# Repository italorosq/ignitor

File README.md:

# Serra Rocketry Ignitor

Sistema de ignição remota para foguetes experimentais. Duas estações
independentes conversam por LoRa 433 MHz.

A mesma PCB é usada nas duas estações para baratear a fabricação. O que muda é
a população e o firmware:

| Estação | Firmware | Módulos ligados |
| --- | --- | --- |
| Comando | `estacao_comando_esp.py` | botão, OLED, LEDs, buzzer, LoRa |
| Ignição | `estacao_ignicao_esp.py` | relé, Q1/Q2, LEDs, buzzer, LoRa |

Na estação de comando não são montados Q1, Q2, J7/J8/J12 nem o módulo relé. Na
ignição, o OLED (J11) não é montado. O resto da placa é comum.

## Como funciona

1. O operador segura o botão até o OLED mostrar **CONFIRMADO** (cerca de 13 s).
2. O comando transmite `ARM_CONFIRMED` a cada 200 ms.
3. A ignição responde `ACK` e começa a contagem de **10 s**.
4. Se o comando sumir por mais de **500 ms**, a ignição aborta.
5. No fim da contagem, o relé e o Q1 fecham por **2 s**.
6. A ignição envia `IGNITION_COMPLETE`. O comando mostra o resultado no OLED e
   toca o tema do Mario no buzzer.
7. Soltar o botão a qualquer momento, inclusive durante a queima, envia `ABORT`.
8. Depois da queima ou de um abort, o comando espera o botão ser solto e
   pressionado de novo antes de iniciar outro ciclo.

Ao energizar, o comando toca o tema do **Zelda**. Enquanto o botão está
pressionado, dá um bip curto por segundo. No fim da queima, toca o tema do
**Mario**. O laço de disparo usa duas chaves em série: o contato do relé e o Q1. O Q1 fica
no lado de baixo:

```text
BAT+ ── relé COM/NO ── ignitor ── J12.2 (dreno Q1)
Q1 source (J12.1) ──────────────── BAT−
```

Não ligue o ignitor entre J12.1 e J12.2: isso coloca a carga em paralelo com o
Q1. Também não inverta dreno e source; o diodo de corpo do MOSFET conduz e a
carga dispara mesmo com `GATE_2` em zero.

## Firmware

- Comando: `firmware/micropython/estacao_comando_esp.py` (ESP32 + OLED).
- Ignição: `firmware/micropython/estacao_ignicao_esp.py` (ESP32, sem OLED).
- Pico: `firmware/micropython/legacy/` (não é usado nas placas atuais).

Os dois firmwares são independentes. O comando não carrega código de relé ou
ADC; a ignição não carrega código de OLED, botão ou EXP.

## Placas

| Placa | Dimensão | Estado |
| --- | --- | --- |
| Ignição SMD | 78,8 × 57,3 mm | candidata; conferir DRC antes de fabricar |
| Ignição PTH | 75 × 80 mm | funcional; limpeza de serigrafia pendente |
| Ignição CNC | 50 × 90 mm | em projeto |

## Segurança

- Use carga dummy antes de qualquer ignitor real.
- Conecte a antena LoRa antes de energizar.
- Feche o J8 (ARM/RBF) só no momento do teste.
- Mantenha o operador a pelo menos 10 m do foguete.
- O botão de comando é momentâneo: soltar a qualquer momento aborta na hora.
  Só solte depois de o OLED mostrar `CONFIRMADO`.
- Depois de um abort ou de uma queima, solte o botão antes de tentar de novo.
- A ignição não tem botão local; o abort vem por LoRa ou pela perda de sinal.
- O link do comando é supervisão: quem corta o disparo é a ignição, em 500 ms.
- O protocolo usa ID de sistema e sequência, mas não tem criptografia. O J8
  continua sendo a barreira física.

## Documentação

- [Arquitetura](docs/ARQUITETURA.md)
- [Instalação](docs/INSTALL.md)
- [Protocolo](docs/README_API.md)
- [Estado do projeto](docs/ESTADO_DO_PROJETO.md)
- [Testes](test/README.md)

Projeto da [Serra Rocketry](https://github.com/Serra-Rocketry).

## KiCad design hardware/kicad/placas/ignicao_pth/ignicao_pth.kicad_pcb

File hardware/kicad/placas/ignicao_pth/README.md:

# Ignição PTH

Placa de 75 × 80 mm, duas camadas, quatro furos M3. Mesma topologia da SMD;
mudam os encapsulamentos (D1 1N5818, C3 de 10 µF e Q3 BC337).

## Estado

- DRC: 0 erros, 100 avisos (serigrafia e biblioteca), 0 desconexões.
- Paridade: 4 itens, todos os furos `H1`–`H4`.
- `Q1.3`/`J9.1` no GND; `Q1.2`/`J9.2` no dreno. O `J9.1` é o retorno
  BAT−/GND; o `J9.2` é o NO do relé/dreno.
- Pacote JLCPCB antigo; regenerar antes de fabricar.

## Conectores

| Ref | Uso |
| --- | --- |
| J1 | entrada 5 V |
| J2/J3 | botão (comando) |
| J4/J5 | LED do botão (comando) |
| J7 | módulo relé (ignição) |
| J8 | ARM/RBF (ignição) |
| J9 | dreno/source do Q1 (ignição) |
| J10 | buzzer |
| J11 | OLED (comando) |

## Validação

```powershell
$cli = "C:\Program Files\KiCad\10.0\bin\kicad-cli.exe"
& $cli sch erc --severity-all ignicao_pth.kicad_sch
& $cli pcb drc --severity-all --schematic-parity ignicao_pth.kicad_pcb
```

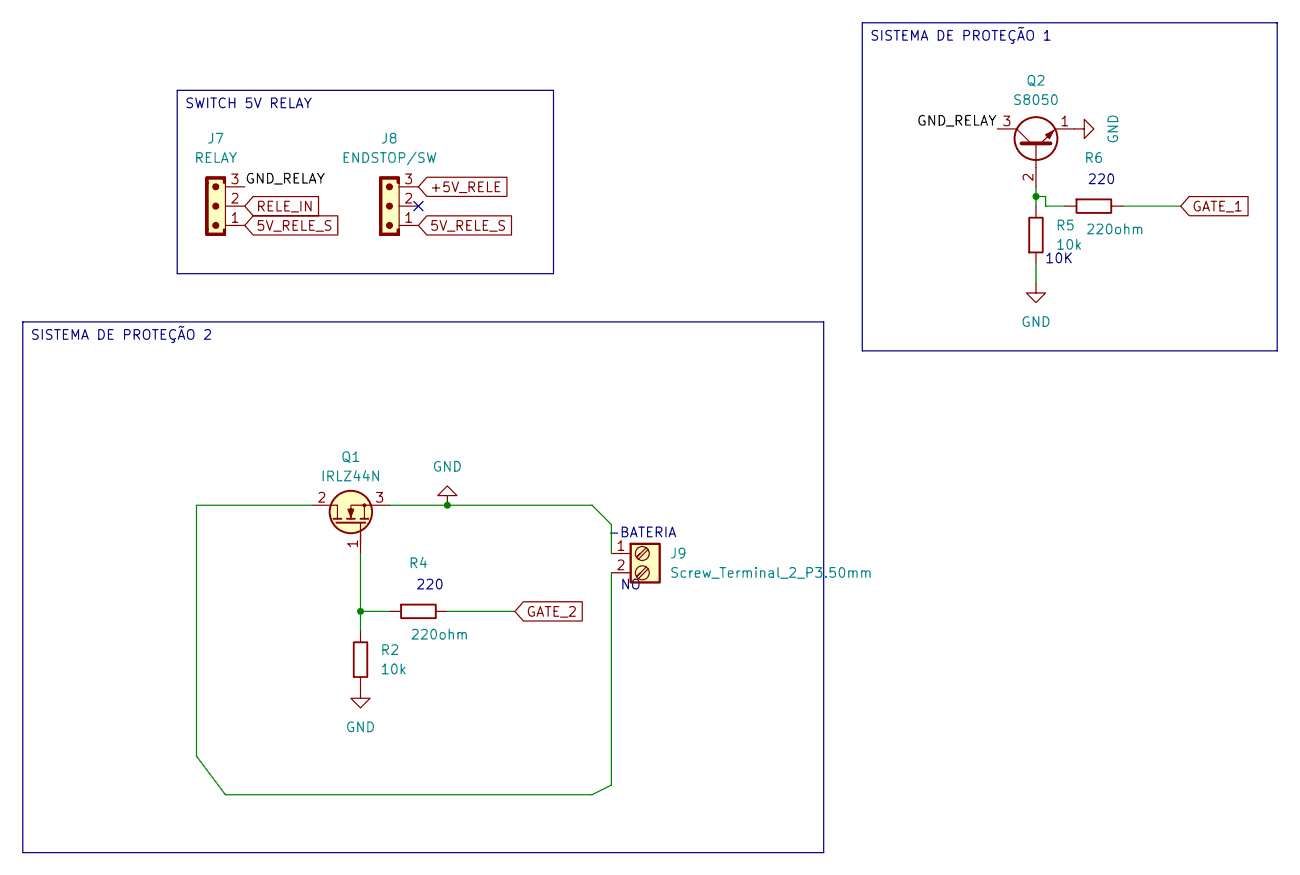
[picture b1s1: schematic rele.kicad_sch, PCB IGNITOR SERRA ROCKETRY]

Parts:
J7: RELAY; JST_EH_B3B-EH-A_1x03_P2.50mm_Vertical
J8: ENDSTOP/SW; JST_EH_B3B-EH-A_1x03_P2.50mm_Vertical
J9: Screw_Terminal_2_P3.50mm; TerminalBlock_Phoenix_PT-1,5-2-3.5-H_1x02_P3.50mm_Horizontal
Q1: IRLZ44N; TO-220-3_Vertical_GDS
Q2: S8050; TO-92_Inline
R2, R5: 10k; R_Axial_DIN0207_L6.3mm_D2.5mm_P10.16mm_Horizontal
R4, R6: 220ohm; R_Axial_DIN0207_L6.3mm_D2.5mm_P10.16mm_Horizontal

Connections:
5V_RELE_S: J7.1, J8.1
+5V_RELE: J8.3; also elsewhere on the board
/rele/GND_RELAY: J7.3, Q2.3 (C)
GATE_1: R6.2; also elsewhere on the board
GATE_2: R4.2; also elsewhere on the board
GND: J9.1, Q1.3 (S), Q2.1 (E), R2.1, R5.1; also elsewhere on the board
unnamed: J9.2, Q1.2 (D)
unnamed: Q1.1 (G), R2.2, R4.1
unnamed: Q2.2 (B), R5.2, R6.1
RELE_IN: J7.2; also elsewhere on the board

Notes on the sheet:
220
-BATERIA
10K
SISTEMA DE PROTEÇÃO 1
SWITCH 5V RELAY
SISTEMA DE PROTEÇÃO 2

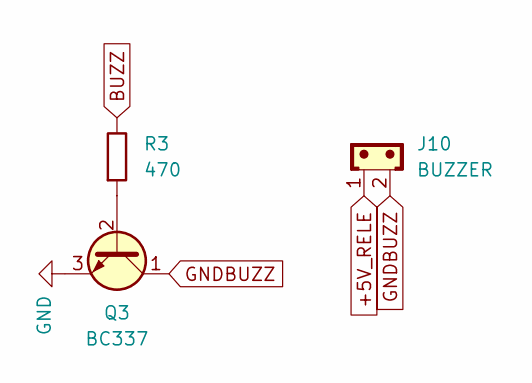
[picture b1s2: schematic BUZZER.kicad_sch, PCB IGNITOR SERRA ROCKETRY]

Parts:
J10: BUZZER; JST_EH_B2B-EH-A_1x02_P2.50mm_Vertical
Q3: BC337; TO-92_Inline_Wide_CBE
R3: 470; R_Axial_DIN0207_L6.3mm_D2.5mm_P10.16mm_Horizontal

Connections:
+5V_RELE: J10.1; also elsewhere on the board
BUZZ: R3.2; also elsewhere on the board
GND: Q3.3 (E); also elsewhere on the board
GNDBUZZ: J10.2, Q3.1 (C)
unnamed: Q3.2 (B), R3.1

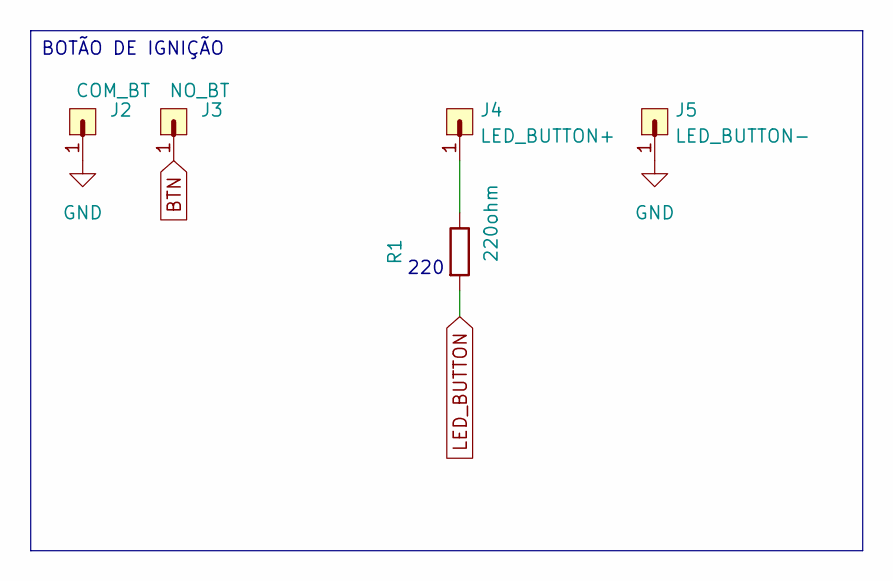
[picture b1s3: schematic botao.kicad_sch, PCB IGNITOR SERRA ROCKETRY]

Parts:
J2: COM_BT; PinHeader_1x01_P2.54mm_Vertical
J3: NO_BT; PinHeader_1x01_P2.54mm_Vertical
J4: LED_BUTTON+; PinHeader_1x01_P2.54mm_Vertical
J5: LED_BUTTON-; PinHeader_1x01_P2.54mm_Vertical
R1: 220ohm; R_Axial_DIN0207_L6.3mm_D2.5mm_P10.16mm_Horizontal

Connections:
BTN: J3.1; also elsewhere on the board
GND: J2.1, J5.1; also elsewhere on the board
LED_BUTTON: R1.1; also elsewhere on the board
unnamed: J4.1, R1.2

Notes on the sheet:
220
BOTÃO DE IGNIÇÃO

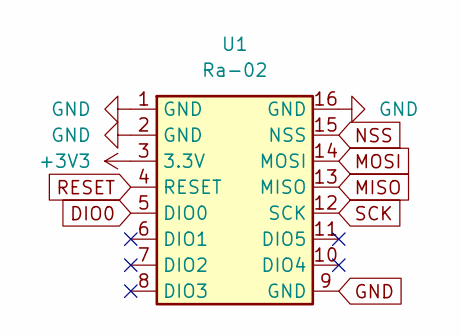
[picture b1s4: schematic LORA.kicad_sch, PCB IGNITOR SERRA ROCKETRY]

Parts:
U1: Ra-02; RA-02_THT

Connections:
+3V3: U1.3 (3.3V); also elsewhere on the board
DIO0: U1.5 (DIO0); also elsewhere on the board
GND: U1.1 (GND), U1.2 (GND), U1.9 (GND), U1.16 (GND); also elsewhere on the board
MISO: U1.13 (MISO); also elsewhere on the board
MOSI: U1.14 (MOSI); also elsewhere on the board
NSS: U1.15 (NSS); also elsewhere on the board
RESET: U1.4 (RESET); also elsewhere on the board
SCK: U1.12 (SCK); also elsewhere on the board

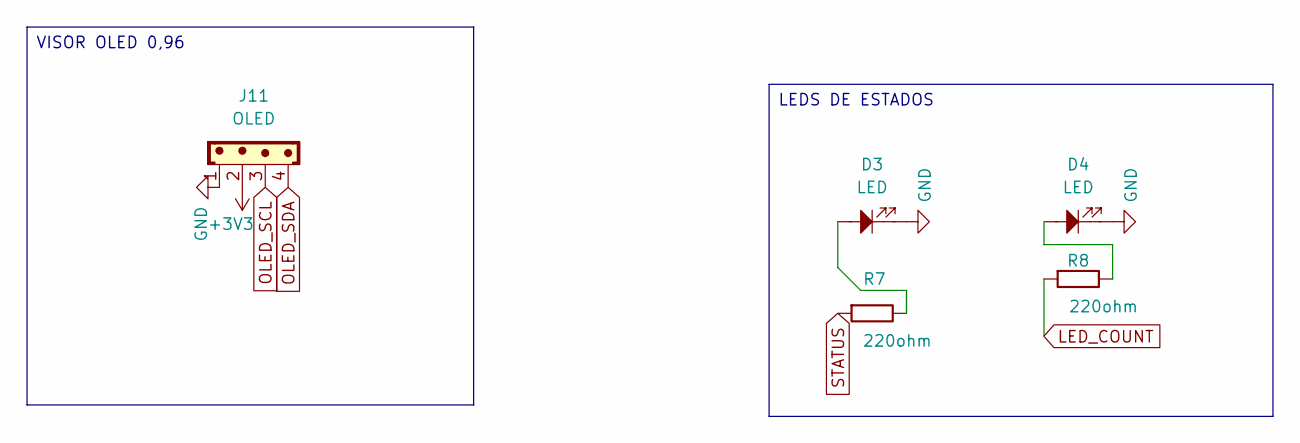
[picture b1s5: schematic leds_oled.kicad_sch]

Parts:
D3, D4: LED; LED_D5.0mm
J11: OLED; JST_EH_B4B-EH-A_1x04_P2.50mm_Vertical
R7, R8: 220ohm; R_Axial_DIN0207_L6.3mm_D2.5mm_P10.16mm_Horizontal

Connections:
+3V3: J11.2; also elsewhere on the board
GND: D3.1, D4.1, J11.1; also elsewhere on the board
LED_COUNT: R8.1; also elsewhere on the board
unnamed: D3.2, R7.2
unnamed: D4.2, R8.2
OLED_SCL: J11.3; also elsewhere on the board
OLED_SDA: J11.4; also elsewhere on the board
STATUS: R7.1; also elsewhere on the board

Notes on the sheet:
LEDS DE ESTADOS
VISOR OLED 0,96

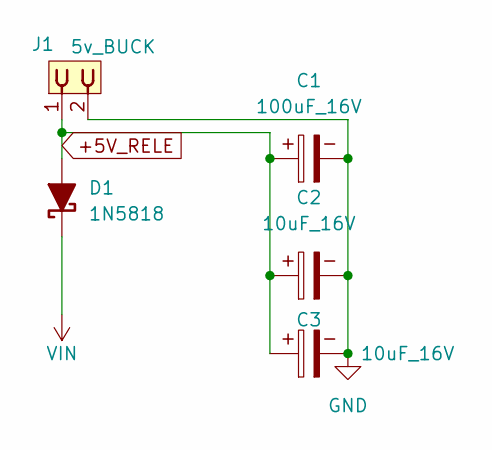
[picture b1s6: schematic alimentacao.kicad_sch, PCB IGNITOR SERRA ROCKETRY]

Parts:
C1: 100uF_16V; CP_Radial_D5.0mm_P2.00mm
C2, C3: 10uF_16V; CP_Radial_D5.0mm_P2.00mm
D1: 1N5818; D_DO-41_SOD81_P7.62mm_Horizontal
J1: 5v_BUCK; PinSocket_1x02_P2.54mm_Vertical

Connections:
+5V_RELE: C1.1, C2.1, C3.1, D1.2 (A), J1.1; also elsewhere on the board
GND: C1.2, C2.2, C3.2, J1.2; also elsewhere on the board
VIN: D1.1 (K); also elsewhere on the board

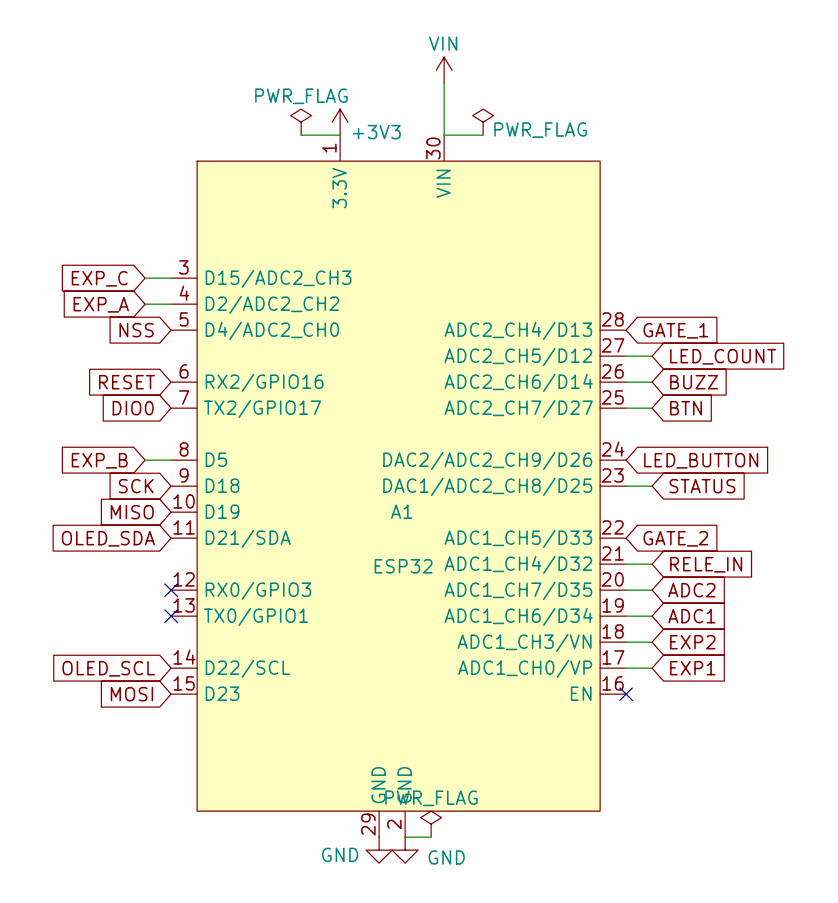
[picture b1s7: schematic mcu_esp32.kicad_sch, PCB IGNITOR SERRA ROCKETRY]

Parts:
A1: ESP32; DOIT_ESP32_DEVKIT_30Pins

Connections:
+3V3: A1.1 (3.3V); also elsewhere on the board
ADC1: A1.19 (ADC1_CH6/D34)
ADC2: A1.20 (ADC1_CH7/D35)
BTN: A1.25 (ADC2_CH7/D27); also elsewhere on the board
BUZZ: A1.26 (ADC2_CH6/D14); also elsewhere on the board
DIO0: A1.7 (TX2/GPIO17); also elsewhere on the board
EXP1: A1.17 (ADC1_CH0/VP)
EXP2: A1.18 (ADC1_CH3/VN)
EXP_A: A1.4 (D2/ADC2_CH2)
EXP_B: A1.8 (D5)
EXP_C: A1.3 (D15/ADC2_CH3)
GATE_1: A1.28 (ADC2_CH4/D13); also elsewhere on the board
GATE_2: A1.22 (ADC1_CH5/D33); also elsewhere on the board
GND: A1.2 (GND), A1.29 (GND); also elsewhere on the board
LED_BUTTON: A1.24 (DAC2/ADC2_CH9/D26); also elsewhere on the board
LED_COUNT: A1.27 (ADC2_CH5/D12); also elsewhere on the board
MISO: A1.10 (D19); also elsewhere on the board
MOSI: A1.15 (D23); also elsewhere on the board
NSS: A1.5 (D4/ADC2_CH0); also elsewhere on the board
OLED_SCL: A1.14 (D22/SCL); also elsewhere on the board
OLED_SDA: A1.11 (D21/SDA); also elsewhere on the board
RELE_IN: A1.21 (ADC1_CH4/D32); also elsewhere on the board
RESET: A1.6 (RX2/GPIO16); also elsewhere on the board
SCK: A1.9 (D18); also elsewhere on the board
STATUS: A1.23 (DAC1/ADC2_CH8/D25); also elsewhere on the board
VIN: A1.30 (VIN); also elsewhere on the board

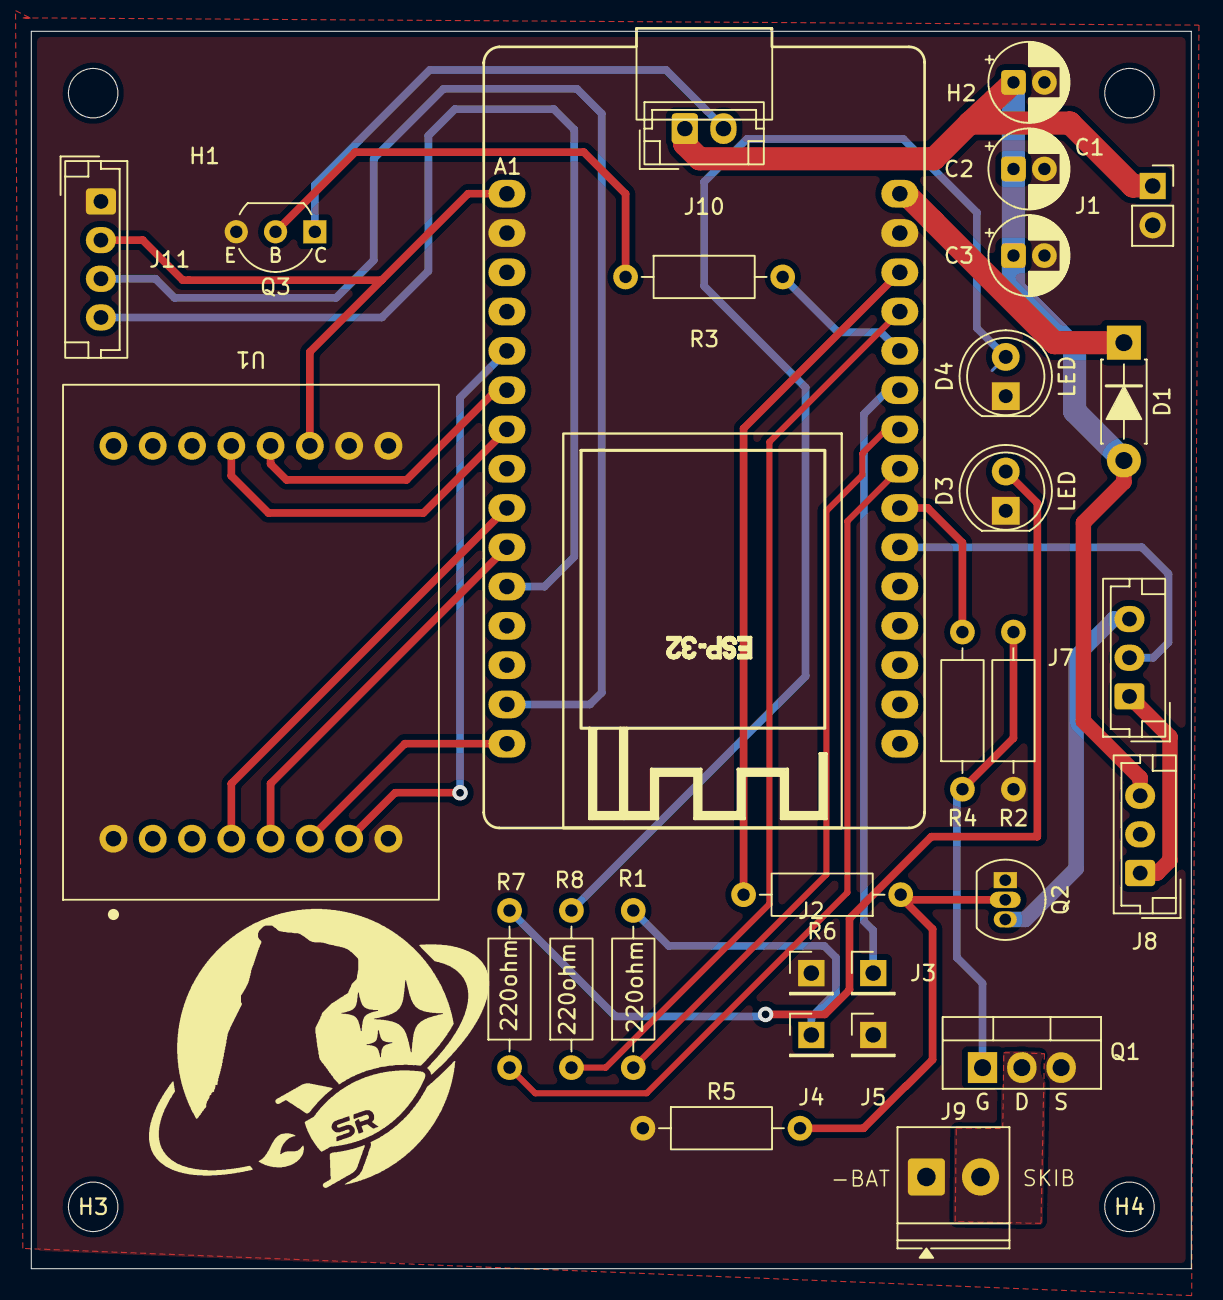
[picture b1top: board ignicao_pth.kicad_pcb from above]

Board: 2 copper layers, 75.0 x 80.0 mm, 33 parts (0 on the bottom side), 30 nets.

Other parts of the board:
H1, H2, H3, H4: MountingHole_3.2mm_M3

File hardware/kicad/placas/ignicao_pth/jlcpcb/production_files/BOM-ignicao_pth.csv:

Comment,Designator,Footprint,LCSC,Quantity
IRLZ44N,Q1,TO-220-3_Vertical_GDS,,1
LED,D3,LED_D5.0mm,,1
10uF_16V,C2,CP_Radial_D5.0mm_P2.00mm,,1
ENDSTOP/SW,J8,JST_EH_B3B-EH-A_1x03_P2.50mm_Vertical,,1
BUZZER,J10,JST_EH_B2B-EH-A_1x02_P2.50mm_Vertical,,1
LED,D4,LED_D5.0mm,,1
10k,R2,R_Axial_DIN0207_L6.3mm_D2.5mm_P10.16mm_Horizontal,,1
470,R3,R_Axial_DIN0207_L6.3mm_D2.5mm_P10.16mm_Horizontal,,1
Ra-02,U1,RA-02_THT,,1
100uF_16V,C1,CP_Radial_D5.0mm_P2.00mm,,1
OLED,J11,JST_EH_B4B-EH-A_1x04_P2.50mm_Vertical,,1
S8050,Q2,TO-92_Inline,,1
LED_BUTTON-,J5,PinHeader_1x01_P2.54mm_Vertical,,1
COM_BT,J2,PinHeader_1x01_P2.54mm_Vertical,,1
220ohm,R6,R_Axial_DIN0207_L6.3mm_D2.5mm_P10.16mm_Horizontal,,1
10uF_16V,C3,CP_Radial_D5.0mm_P2.00mm,,1
NO_BT,J3,PinHeader_1x01_P2.54mm_Vertical,,1
5v_BUCK,J1,PinSocket_1x02_P2.54mm_Vertical,,1
RELAY,J7,JST_EH_B3B-EH-A_1x03_P2.50mm_Vertical,,1
220ohm,R4,R_Axial_DIN0207_L6.3mm_D2.5mm_P10.16mm_Horizontal,,1
ESP32,A1,DOIT_ESP32_DEVKIT_30Pins,,1
LED_BUTTON+,J4,PinHeader_1x01_P2.54mm_Vertical,,1
220ohm,R1,R_Axial_DIN0207_L6.3mm_D2.5mm_P10.16mm_Horizontal,,1
220ohm,R7,R_Axial_DIN0207_L6.3mm_D2.5mm_P10.16mm_Horizontal,,1
Screw_Terminal_2_P3.50mm,J9,"TerminalBlock_Phoenix_PT-1,5-2-3.5-H_1x02_P3.50mm_Horizontal",,1
10k,R5,R_Axial_DIN0207_L6.3mm_D2.5mm_P10.16mm_Horizontal,,1
1N5818,D1,D_DO-41_SOD81_P7.62mm_Horizontal,,1
BC337,Q3,TO-92_Inline_Wide_CBE,,1
220ohm,R8,R_Axial_DIN0207_L6.3mm_D2.5mm_P10.16mm_Horizontal,,1

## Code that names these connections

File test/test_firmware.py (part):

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    "PIN_MISO": 19,
    "PIN_CS": 4,
    "PIN_RESET": 16,
    "PIN_DIO0": 17,
    "PIN_LED_YELLOW": 25,
    "PIN_LED_RED": 12,
    "PIN_LED_LINK": 26,
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)

PROIBIDOS_COMANDO = (
    "PIN_RELE", "PIN_GATE_1", "PIN_GATE_2",
    "PIN_EXP_A", "PIN_EXP_B", "PIN_EXP_C",
    "PIN_ADC1_IN1", "PIN_ADC1_IN2",
)
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
    # O rele esta no pino fisico 21 do modulo, que e GPIO32.
    assert MAPA_KICAD["RELE_IN"] == (21, 32)
    assert ign["PIN_RELE_NUM"] == MAPA_KICAD["RELE_IN"][1]

    for nome, constante in (
        ("GATE_2", "PIN_GATE_2_NUM"),
        ("GATE_1", "PIN_GATE_1_NUM"),
        ("BUZZ", "PIN_BUZZER_NUM"),
        ("STATUS", "PIN_STATUS_NUM"),
        ("LED_COUNT", "PIN_LED_COUNT_NUM"),
        ("NSS", "PIN_LORA_CS_NUM"),
        ("RESET", "PIN_LORA_RESET_NUM"),
        ("DIO0", "PIN_LORA_DIO0_NUM"),
    ):
        assert ign[constante] == MAPA_KICAD[nome][1], (nome, constante)

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    for nome, constante in (
        ("NSS", "PIN_CS"),
        ("RESET", "PIN_RESET"),
        ("DIO0", "PIN_DIO0"),
        ("SCK", "PIN_SCK"),
        ("MISO", "PIN_MISO"),
        ("MOSI", "PIN_MOSI"),
        ("BTN", "PIN_BUTTON"),
        ("BUZZ", "PIN_BUZZER"),
        ("STATUS", "PIN_LED_YELLOW"),
        ("LED_COUNT", "PIN_LED_RED"),
        ("LED_BUTTON", "PIN_LED_LINK"),
        ("OLED_SDA", "PIN_I2C_SDA"),
        ("OLED_SCL", "PIN_I2C_SCL"),
    ):
        assert cmd[constante] == MAPA_KICAD[nome][1], (nome, constante)

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    assert consts["RELE_ACTIVE_LEVEL"] == 0

    valores = _pinos_com_valor(IGNICAO)
    assert valores["PIN_GATE_1"] == 0
    assert valores["PIN_GATE_2"] == 0


def test_desarme_abre_q1_antes_do_rele():
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
    for caminho in (BANCADA / "mp_teste_rele.py", BANCADA / "mp_teste_transistor.py"):
        valores = _pinos_com_valor(caminho)
        assert valores.get("PIN_GATE_1") == 0, f"{caminho.name}: GATE_1"
        assert valores.get("PIN_GATE_2") == 0, f"{caminho.name}: GATE_2"
        assert valores.get("PIN_RELE") == ("nome", "RELE_INACTIVE_LEVEL"), f"{caminho.name}: RELE"

    ordem = _ordem_chamadas(BANCADA / "mp_teste_transistor.py", "desligar_tudo")
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
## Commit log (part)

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2026-04-17 Refactor firmware and documentation for LoRa ignition system
    - Updated README.md to reflect changes in architecture and data flow for command and ignition stations.
    - Modified config.example.h to change LoRa frequency to 433 MHz and updated pin assignments.
    - Revised hardware documentation to clarify pin connections and functionality.
    - Enhanced command_station.py and ignition_station.py with improved state management and link validation using PING/PONG messages.
    - Updated test procedures to align with new command protocols and pin configurations.
    - Removed legacy code for ESP32/ESP8266 from code.ino, retaining it only for historical reference.
2026-04-17 Refatorar driver LoRa para suporte a fallback nativo e melhorias na estrutura do código
2026-04-18 Adicionar suporte a driver LoRa nativo com melhorias na compatibilidade e estrutura do código
2026-04-18 Adicionar documentação sobre envio de código para Raspberry Pi Pico e créditos da biblioteca LoRa
2026-04-21 Adicionar lógica de pisca LED de link para indicar estado de conexão
2026-04-21 Adicionar diretiva para ignorar cache do Python
2026-04-21 Adicionar documentação detalhada sobre instalação, API, envio de código, resultados de testes e troubleshooting
2026-04-21 Add LoRa radio utility and connection tests for MicroPython
    - Implement LoRaRadio class for SX1278 with support for both modern and legacy APIs.
    - Create mp_teste_conexao.py for PING/PONG connection testing between two devices.
    - Develop mp_teste_envio_dados.py for data transmission with ACK handling.
    - Include LED feedback for transmission and reception events.
    - Add summary statistics for connection tests and data transmission.
2026-04-22 docs: reorganiza estrutura e padroniza hardware para ESP32-C3
2026-04-22 docs(firmware): atualizar README para refletir estrutura atual
